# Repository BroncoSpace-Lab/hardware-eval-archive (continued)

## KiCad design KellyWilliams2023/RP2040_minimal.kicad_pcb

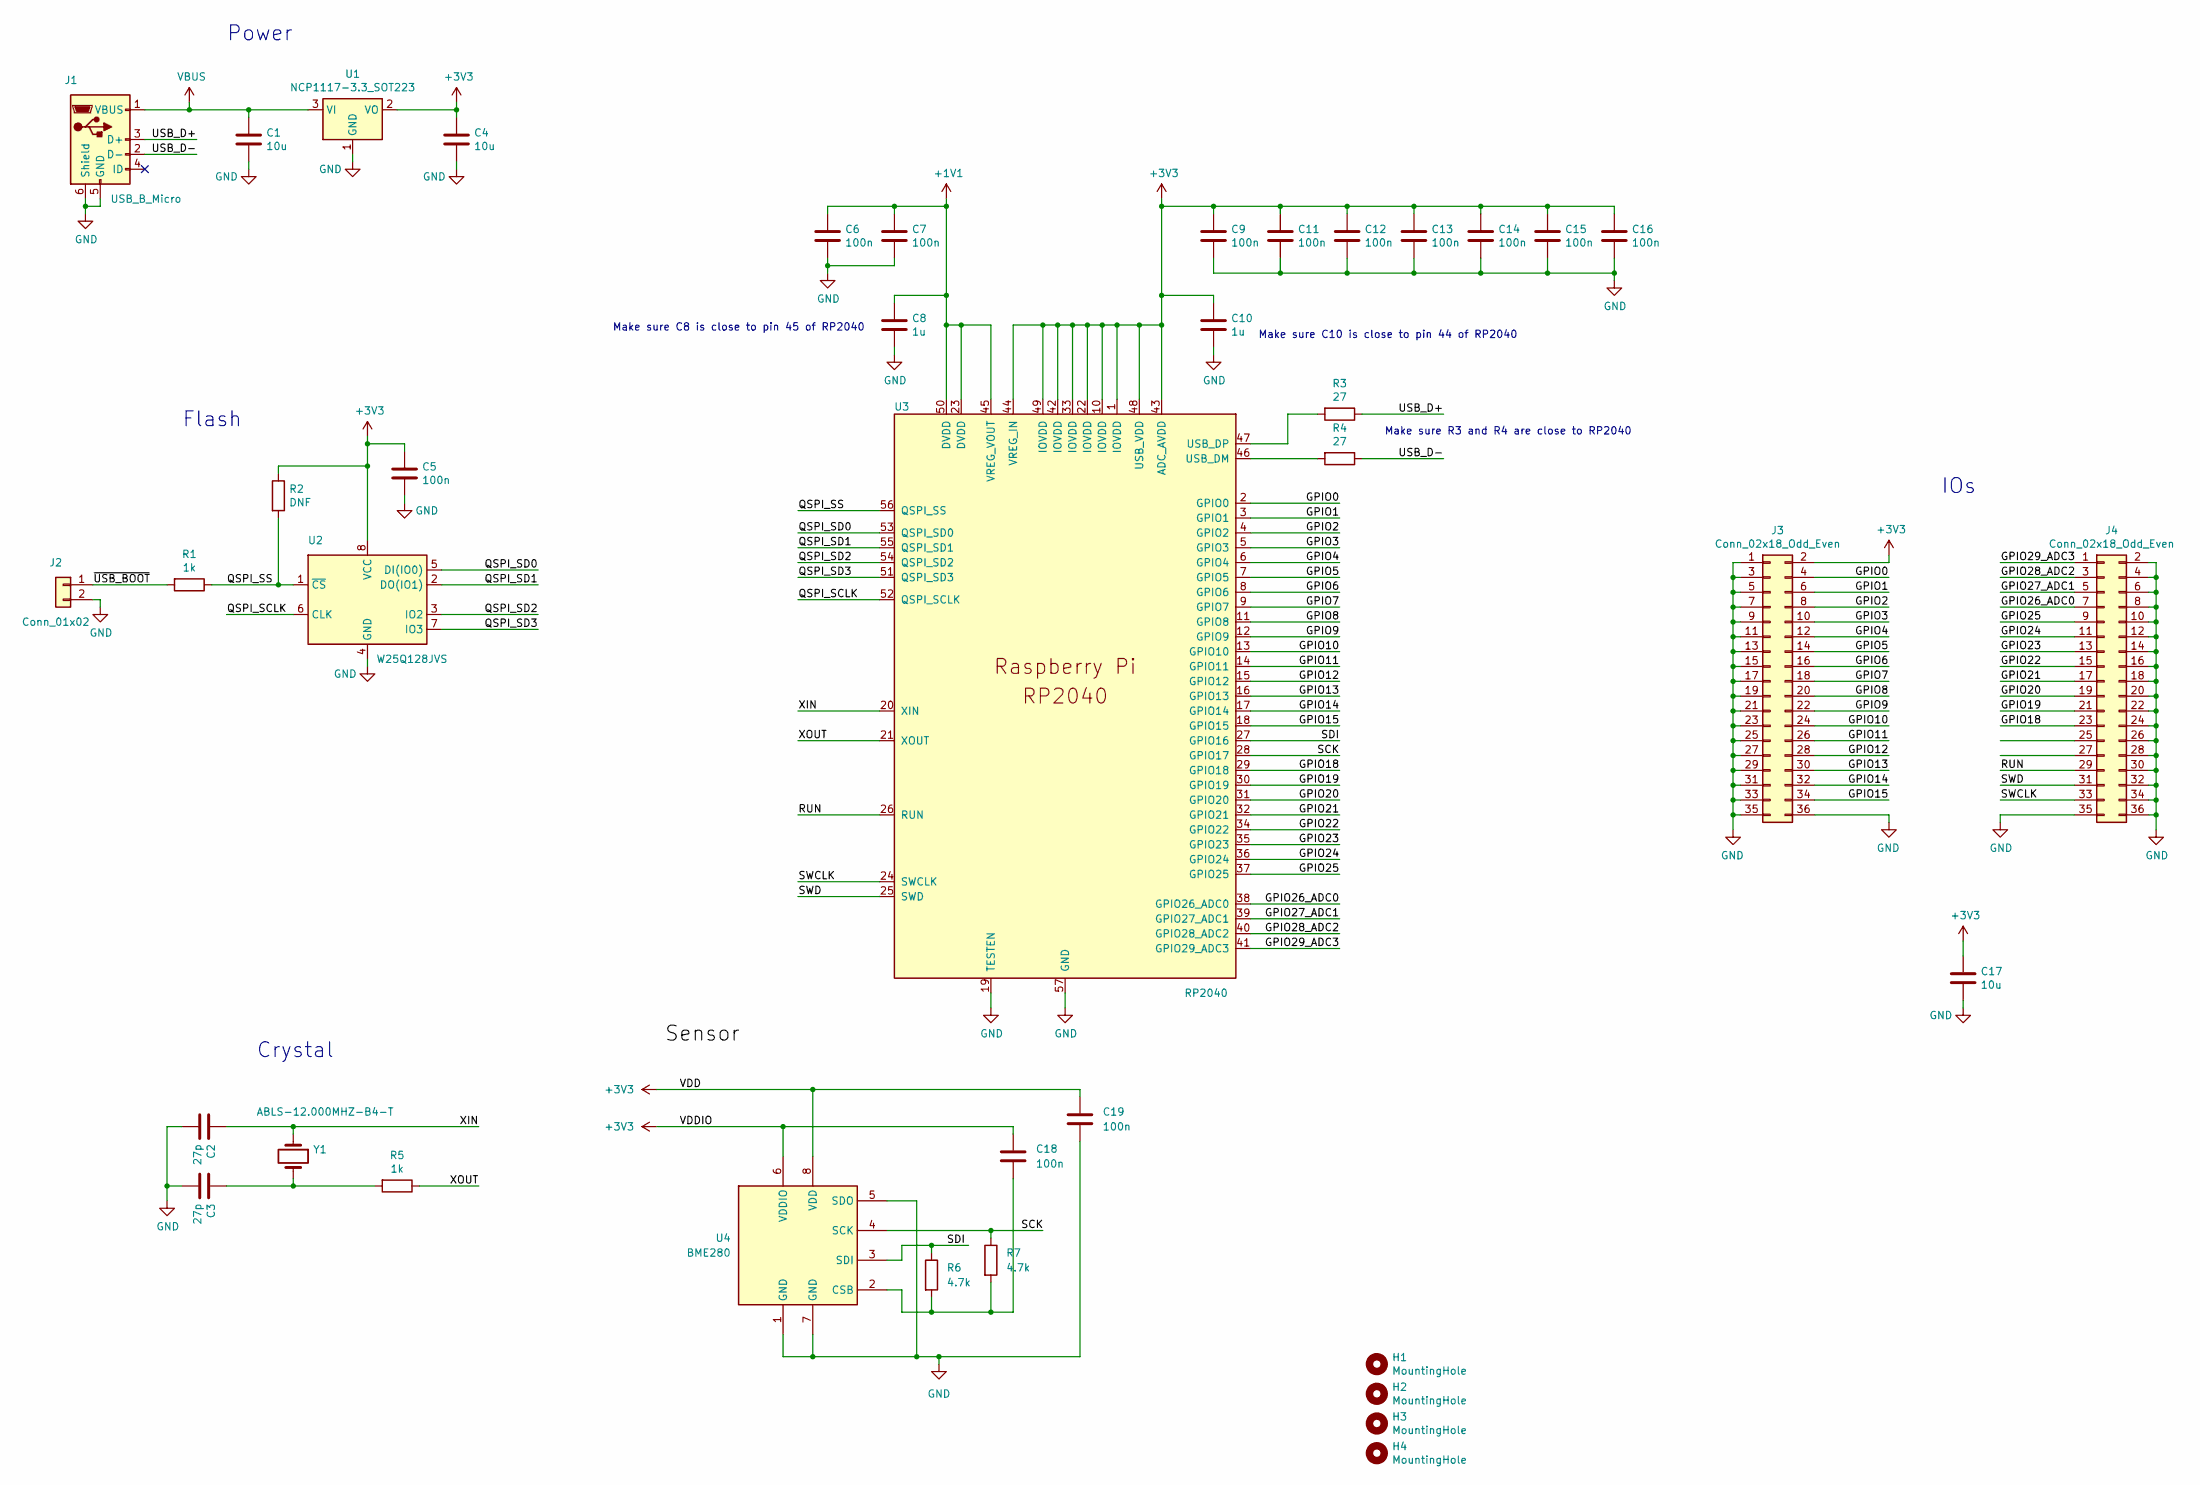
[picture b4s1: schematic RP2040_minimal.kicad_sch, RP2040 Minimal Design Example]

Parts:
C1, C4, C17: 10u; C_0805_2012Metric
C2, C3: 27p; C_0402_1005Metric
C5, C6, C7, C9, C11, C12, C13, C14, C15, C16, C18, C19: 100n; C_0402_1005Metric
C8, C10: 1u; C_0402_1005Metric
H1, H2, H3, H4: MountingHole; MountingHole_2.7mm_M2.5
J1: USB_B_Micro; USB_Micro-B_Amphenol_10103594-0001LF_Horizontal_modified
J2: Conn_01x02; PinHeader_1x02_P2.54mm_Vertical
J3, J4: Conn_02x18_Odd_Even; PinHeader_2x18_P2.54mm_Vertical
R1, R5: 1k; C_0402_1005Metric
R2: DNF; C_0402_1005Metric
R3, R4: 27; C_0402_1005Metric
R6, R7: 4.7k; C_0402_1005Metric
U1: NCP1117-3.3_SOT223; SOT-223-3_TabPin2
U2: W25Q128JVS; SOIC-8_5.23x5.23mm_P1.27mm
U3: RP2040; RP2040-QFN-56
U4: BME280; Bosch_LGA-8_2.5x2.5mm_P0.65mm_ClockwisePinNumbering
Y1: ABLS-12.000MHZ-B4-T; Crystal_SMD_HC49-US

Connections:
+1V1: C6.1, C7.1, C8.1, U3.23 (DVDD), U3.45 (VREG_VOUT), U3.50 (DVDD)
+3V3: C4.1, C5.1, C9.1, C10.1, C11.1, C12.1, C13.1, C14.1, C15.1, C16.1, C17.1, C18.1, C19.1, J3.2, R2.1, U1.2 (VO), U2.8 (VCC), U3.1 (IOVDD), U3.10 (IOVDD), U3.22 (IOVDD), U3.33 (IOVDD), U3.42 (IOVDD), U3.43 (ADC_AVDD), U3.44 (VREG_IN), U3.48 (USB_VDD), U3.49 (IOVDD), U4.6 (VDDIO), U4.8 (VDD)
/GPIO0: J3.4, U3.2 (GPIO0)
/GPIO1: J3.6, U3.3 (GPIO1)
/GPIO2: J3.8, U3.4 (GPIO2)
/GPIO3: J3.10, U3.5 (GPIO3)
/GPIO4: J3.12, U3.6 (GPIO4)
/GPIO5: J3.14, U3.7 (GPIO5)
/GPIO6: J3.16, U3.8 (GPIO6)
/GPIO7: J3.18, U3.9 (GPIO7)
/GPIO8: J3.20, U3.11 (GPIO8)
/GPIO9: J3.22, U3.12 (GPIO9)
/GPIO10: J3.24, U3.13 (GPIO10)
/GPIO11: J3.26, U3.14 (GPIO11)
/GPIO12: J3.28, U3.15 (GPIO12)
/GPIO13: J3.30, U3.16 (GPIO13)
/GPIO14: J3.32, U3.17 (GPIO14)
/GPIO15: J3.34, U3.18 (GPIO15)
/GPIO18: J4.23, U3.29 (GPIO18)
/GPIO19: J4.21, U3.30 (GPIO19)
/GPIO20: J4.19, U3.31 (GPIO20)
/GPIO21: J4.17, U3.32 (GPIO21)
/GPIO22: J4.15, U3.34 (GPIO22)
/GPIO23: J4.13, U3.35 (GPIO23)
/GPIO24: J4.11, U3.36 (GPIO24)
/GPIO25: J4.9, U3.37 (GPIO25)
/GPIO26_ADC0: J4.7, U3.38 (GPIO26_ADC0)
/GPIO27_ADC1: J4.5, U3.39 (GPIO27_ADC1)
/GPIO28_ADC2: J4.3, U3.40 (GPIO28_ADC2)
/GPIO29_ADC3: J4.1, U3.41 (GPIO29_ADC3)
/QSPI_SCLK: U2.6 (CLK), U3.52 (QSPI_SCLK)
/QSPI_SD0: U2.5 (DI(IO0)), U3.53 (QSPI_SD0)
/QSPI_SD1: U2.2 (DO(IO1)), U3.55 (QSPI_SD1)
/QSPI_SD2: U2.3 (IO2), U3.54 (QSPI_SD2)
/QSPI_SD3: U2.7 (IO3), U3.51 (QSPI_SD3)
/QSPI_SS: R1.1, R2.2, U2.1 (~CS), U3.56 (QSPI_SS)
/RUN: J4.29, U3.26 (RUN)
/SCK: R7.1, U3.28 (GPIO17), U4.4 (SCK)
/SDI: R6.1, U3.27 (GPIO16), U4.3 (SDI)
/SWCLK: J4.33, U3.24 (SWCLK)
/SWD: J4.31, U3.25 (SWD)
/USB_D+: J1.3 (D+), R3.1
/USB_D-: J1.2 (D-), R4.1
/XIN: C2.1, U3.20 (XIN), Y1.1
/XOUT: R5.1, U3.21 (XOUT)
/~USB_BOOT: J2.1, R1.2
GND: C1.2, C2.2, C3.2, C4.2, C5.2, C6.2, C7.2, C8.2, C9.2, C10.2, C11.2, C12.2, C13.2, C14.2, C15.2, C16.2, C17.2, C19.2, J1.5 (GND), J1.6 (Shield), J2.2, J3.1, J3.3, J3.5, J3.7, J3.9, J3.11, J3.13, J3.15, J3.17, J3.19, J3.21, J3.23, J3.25, J3.27, J3.29, J3.31, J3.33, J3.35, J3.36, J4.2, J4.4, J4.6, J4.8, J4.10, J4.12, J4.14, J4.16, J4.18, J4.20, J4.22, J4.24, J4.26, J4.28, J4.30, J4.32, J4.34, J4.35, J4.36, U1.1 (GND), U2.4 (GND), U3.19 (TESTEN), U3.57 (GND), U4.1 (GND), U4.5 (SDO), U4.7 (GND)
unnamed: C3.1, R5.2, Y1.2
unnamed: R4.2, U3.46 (USB_DM)
unnamed: R3.2, U3.47 (USB_DP)
unnamed: C18.2, R6.2, R7.2, U4.2 (CSB)
VBUS: C1.1, J1.1 (VBUS), U1.3 (VI)

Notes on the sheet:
Make sure C8 is close to pin 45 of RP2040
Make sure C10 is close to pin 44 of RP2040
Power
Crystal
Flash
IOs
Make sure R3 and R4 are close to RP2040

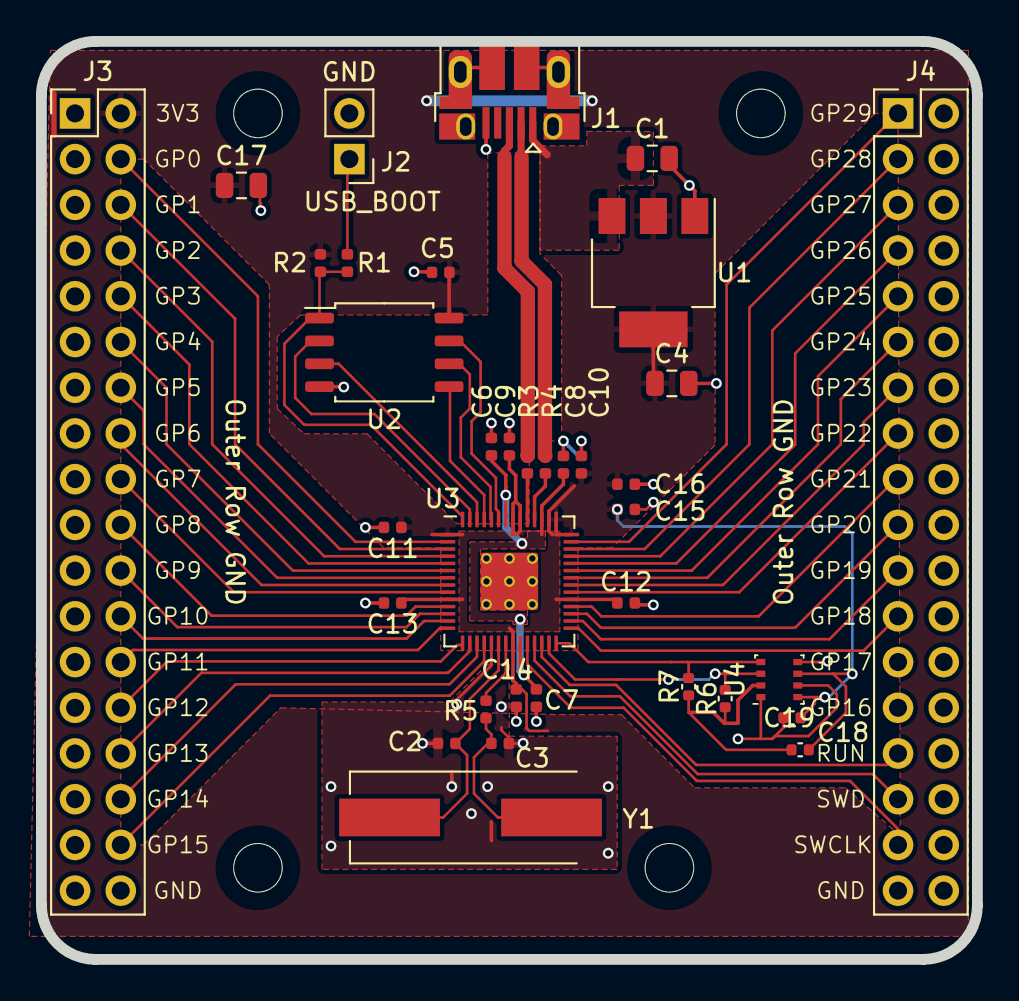
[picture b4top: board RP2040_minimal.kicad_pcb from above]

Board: 2 copper layers, 52.0 x 51.0 mm, 39 parts (0 on the bottom side), 52 nets.

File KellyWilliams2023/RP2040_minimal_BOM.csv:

"Id";"Designator";"Footprint";"Quantity";"Designation";"Supplier and ref";
1;"C4,C1,C17";"C_0805_2012Metric";3;"10u";;;
2;"J1";"USB_Micro-B_Amphenol_10103594-0001LF_Horizontal_modified";1;"USB_B_Micro";;;
3;"J2";"PinHeader_1x02_P2.54mm_Vertical";1;"Conn_01x02";;;
4;"J3,J4";"PinHeader_2x18_P2.54mm_Vertical";2;"Conn_02x18_Odd_Even";;;
5;"C10,C8";"C_0402_1005Metric";2;"1u";;;
6;"C13,C5,C9,C12,C14,C7,C11,C16,C6,C15,C19,C18";"C_0402_1005Metric";12;"100n";;;
7;"R2";"C_0402_1005Metric";1;"DNF";;;
8;"U1";"SOT-223-3_TabPin2";1;"NCP1117-3.3_SOT223";;;
9;"U2";"SOIC-8_5.23x5.23mm_P1.27mm";1;"W25Q128JVS";;;
10;"C3,C2";"C_0402_1005Metric";2;"27p";;;
11;"R1,R5";"C_0402_1005Metric";2;"1k";;;
12;"R3,R4";"C_0402_1005Metric";2;"27";;;
13;"U3";"RP2040-QFN-56";1;"RP2040";;;
14;"H2,H3,H1,H4";"MountingHole_2.7mm_M2.5";4;"MountingHole";;;
15;"Y1";"Crystal_SMD_HC49-US";1;"ABLS-12.000MHZ-B4-T";;;
16;"R6,R7";"C_0402_1005Metric";2;"4.7k";;;
17;"U4";"Bosch_LGA-8_2.5x2.5mm_P0.65mm_ClockwisePinNumbering";1;"BME280";;;

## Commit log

2024-05-24 Update README.md
    Added hyperlinks
2024-05-24 Kelly's Eval
2024-05-29 InitialCommit
    RP2040 Evaluation Board
2024-05-29 Updated stuff
2024-06-05 Noob
    first time using github
2024-06-05 Updated Production Files
2024-06-18 A zip file for the KiCAD schematic and PCB, and Gerber Files
2024-07-02 Leo Zhao Ground Station LNA KiCAD for review
2024-07-09 Unpacked the ZIP File
